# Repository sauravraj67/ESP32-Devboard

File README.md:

# ESP32-Devboard
I made a custom Esp32 board based on ESP32-S3-WROOM-1 , it has a USB type C and i tried to keep the size of the board as small as possible and to have as much as useful pins available on the board.
<br>

<br>
## Overview
This project is a **compact 2-layer development board** based on the **ESP32-S3-WROOM-1 module**. It exposes **all usable GPIOs**, includes onboard **3.3V regulation**, and USB connectivity for easy programming and prototyping. 

## Features
- ESP32-S3-WROOM-1 module (Wi-Fi + Bluetooth 5.0)
- 2-layer compact PCB
- USB connection for programming and power
- Onboard 3.3V voltage regulation

- ## Bill of Materials (BOM)
- 
| Qty | Description |  Total (USD) |
|----|-------------|-------------|
| 1 | PCB and Assembly  |   	71.97 |
| 1 |Shipping JLCPCB - Discount  | 1.72 |

### 💰 Cost Summary
 
- **Estimated Total Cost:** **$73.69 USD**

## Schematic & PCB

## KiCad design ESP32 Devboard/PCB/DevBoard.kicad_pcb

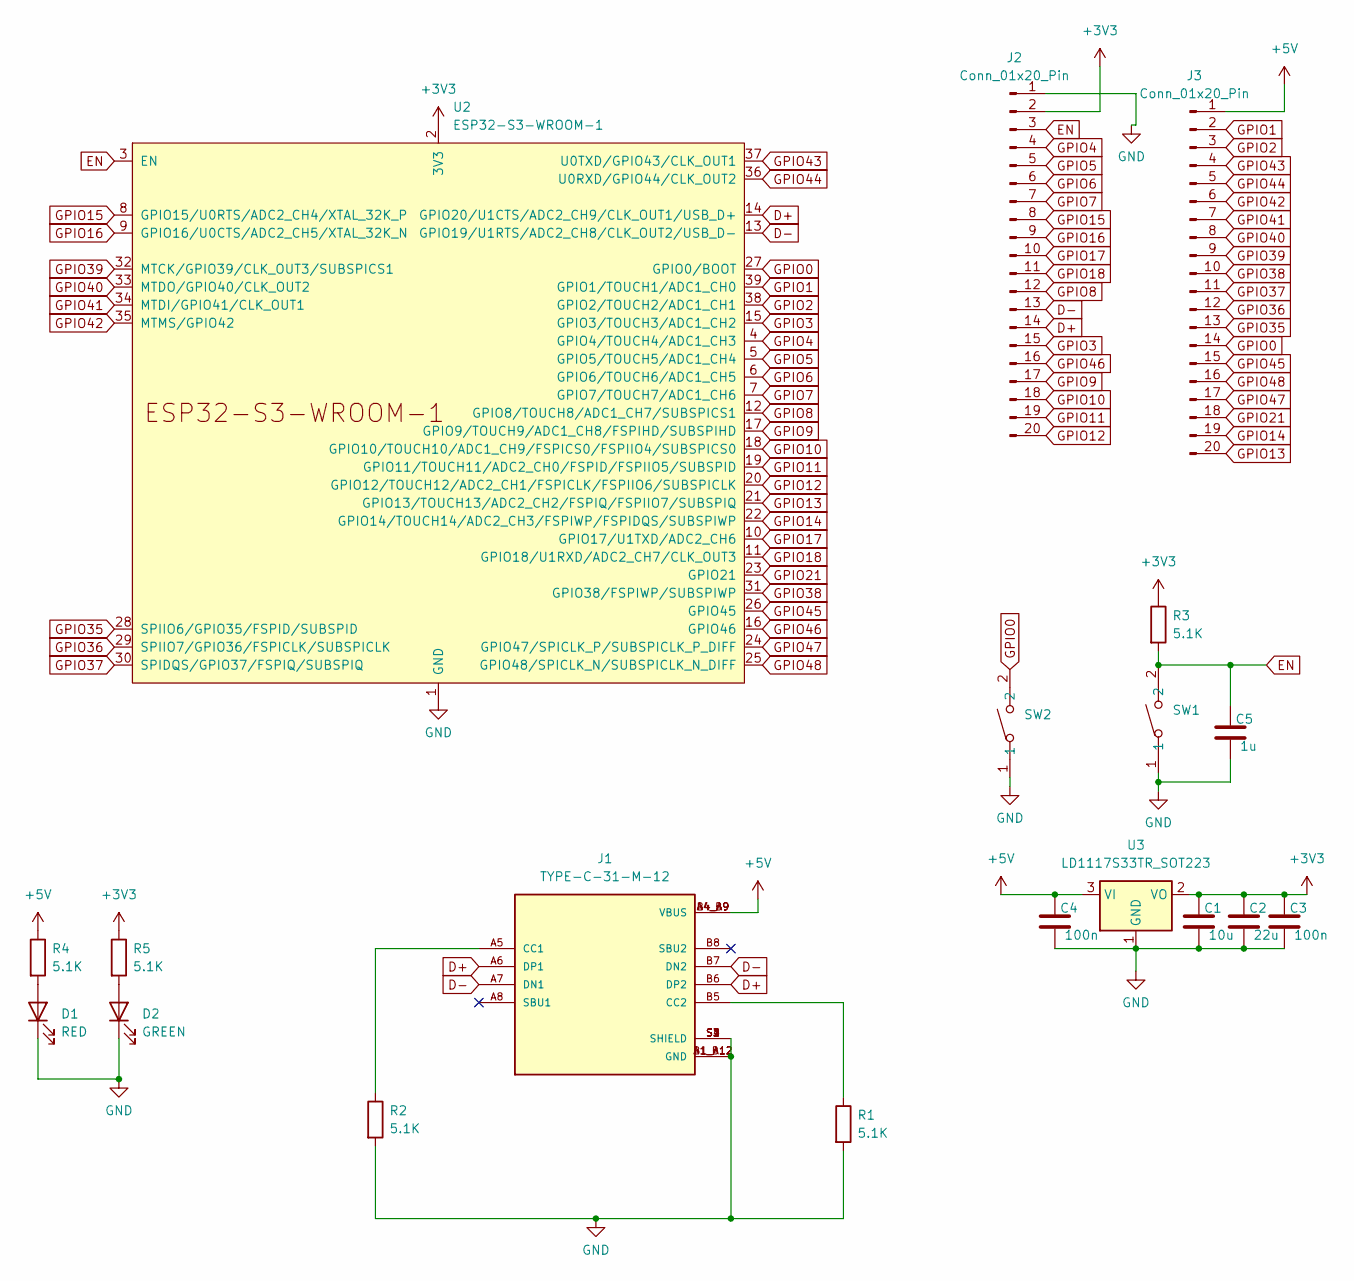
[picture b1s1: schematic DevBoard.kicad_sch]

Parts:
C1: 10u; C_0603_1608Metric
C2: 22u; C_0603_1608Metric
C3, C4: 100n; C_0603_1608Metric
C5: 1u; C_0603_1608Metric
D1: RED; LED_0603_1608Metric
D2: GREEN; LED_0603_1608Metric
J1: TYPE-C-31-M-12; HRO_TYPE-C-31-M-12; PARTREV 2020.12.08
J2, J3: Conn_01x20_Pin; PinHeader_1x20_P2.54mm_Vertical
R1, R2, R3, R4, R5: 5.1K; R_0603_1608Metric
SW1, SW2: TS-1088-AR02016; SW-SMD_L3.9-W3.0-P4.45; LCSC Part C720477
U2: ESP32-S3-WROOM-1
U3: LD1117S33TR_SOT223; SOT-223-3_TabPin2

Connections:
+3V3: C1.1, C2.1, C3.1, J2.2, R3.1, R5.1, U2.2 (3V3), U3.2 (VO)
+5V: C4.1, J1.A4_B9 (VBUS), J1.B4_A9 (VBUS), J3.1, R4.1, U3.3 (VI)
D+: J1.A6 (DP1), J1.B6 (DP2), J2.14, U2.14 (GPIO20/U1CTS/ADC2_CH9/CLK_OUT1/USB_D+)
D-: J1.A7 (DN1), J1.B7 (DN2), J2.13, U2.13 (GPIO19/U1RTS/ADC2_CH8/CLK_OUT2/USB_D-)
EN: C5.1, J2.3, R3.2, SW1.2, U2.3 (EN)
GND: C1.2, C2.2, C3.2, C4.2, C5.2, D1.1 (K), D2.1 (K), J1.A1_B12 (GND), J1.B1_A12 (GND), J1.S1 (SHIELD), J1.S2 (SHIELD), J1.S3 (SHIELD), J1.S4 (SHIELD), J2.1, R1.2, R2.2, SW1.1, SW2.1, U2.1 (GND), U2.40 (GND), U2.41 (GND), U3.1 (GND)
GPIO0: J3.14, SW2.2, U2.27 (GPIO0/BOOT)
GPIO1: J3.2, U2.39 (GPIO1/TOUCH1/ADC1_CH0)
GPIO2: J3.3, U2.38 (GPIO2/TOUCH2/ADC1_CH1)
GPIO3: J2.15, U2.15 (GPIO3/TOUCH3/ADC1_CH2)
GPIO4: J2.4, U2.4 (GPIO4/TOUCH4/ADC1_CH3)
GPIO5: J2.5, U2.5 (GPIO5/TOUCH5/ADC1_CH4)
GPIO6: J2.6, U2.6 (GPIO6/TOUCH6/ADC1_CH5)
GPIO7: J2.7, U2.7 (GPIO7/TOUCH7/ADC1_CH6)
GPIO8: J2.12, U2.12 (GPIO8/TOUCH8/ADC1_CH7/SUBSPICS1)
GPIO9: J2.17, U2.17 (GPIO9/TOUCH9/ADC1_CH8/FSPIHD/SUBSPIHD)
GPIO10: J2.18, U2.18 (GPIO10/TOUCH10/ADC1_CH9/FSPICS0/FSPIIO4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)
GPIO11: J2.19, U2.19 (GPIO11/TOUCH11/ADC2_CH0/FSPID/FSPIIO5/S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)
GPIO12: J2.20, U2.20 (GPIO12/TOUCH12/ADC2_CH1/FSPICLK/FSPIIO6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)
GPIO13: J3.20, U2.21 (GPIO13/TOUCH13/ADC2_CH2/FSPIQ/FSPIIO7/S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)
GPIO14: J3.19, U2.22 (GPIO14/TOUCH14/ADC2_CH3/FSPIWP/FSPIDQS/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)
GPIO15: J2.8, U2.8 (GPIO15/U0RTS/ADC2_CH4/XTAL_32K_P)
GPIO16: J2.9, U2.9 (GPIO16/U0CTS/ADC2_CH5/XTAL_32K_N)
GPIO17: J2.10, U2.10 (GPIO17/U1TXD/ADC2_CH6)
GPIO18: J2.11, U2.11 (GPIO18/U1RXD/ADC2_CH7/CLK_OUT3)
GPIO21: J3.18, U2.23 (GPIO21)
GPIO35: J3.13, U2.28 (SPIIO6/GPIO35/FSPID/SUBSPID)
GPIO36: J3.12, U2.29 (SPIIO7/GPIO36/FSPICLK/SUBSPICLK)
GPIO37: J3.11, U2.30 (SPIDQS/GPIO37/FSPIQ/SUBSPIQ)
GPIO38: J3.10, U2.31 (GPIO38/FSPIWP/SUBSPIWP)
GPIO39: J3.9, U2.32 (MTCK/GPIO39/CLK_OUT3/SUBSPICS1)
GPIO40: J3.8, U2.33 (MTDO/GPIO40/CLK_OUT2)
GPIO41: J3.7, U2.34 (MTDI/GPIO41/CLK_OUT1)
GPIO42: J3.6, U2.35 (MTMS/GPIO42)
GPIO43: J3.4, U2.37 (U0TXD/GPIO43/CLK_OUT1)
GPIO44: J3.5, U2.36 (U0RXD/GPIO44/CLK_OUT2)
GPIO45: J3.15, U2.26 (GPIO45)
GPIO46: J2.16, U2.16 (GPIO46)
GPIO47: J3.17, U2.24 (GPIO47/SPICLK_P/SUBSPICLK_P_DIFF)
GPIO48: J3.16, U2.25 (GPIO48/SPICLK_N/SUBSPICLK_N_DIFF)
unnamed: D1.2 (A), R4.2
unnamed: D2.2 (A), R5.2
unnamed: J1.A5 (CC1), R2.1
unnamed: J1.B5 (CC2), R1.1

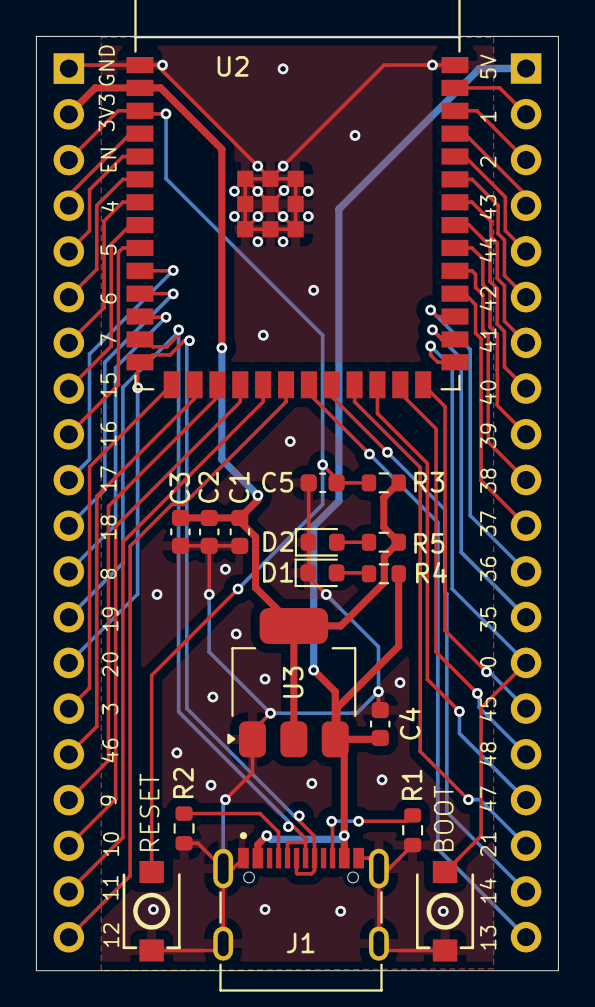
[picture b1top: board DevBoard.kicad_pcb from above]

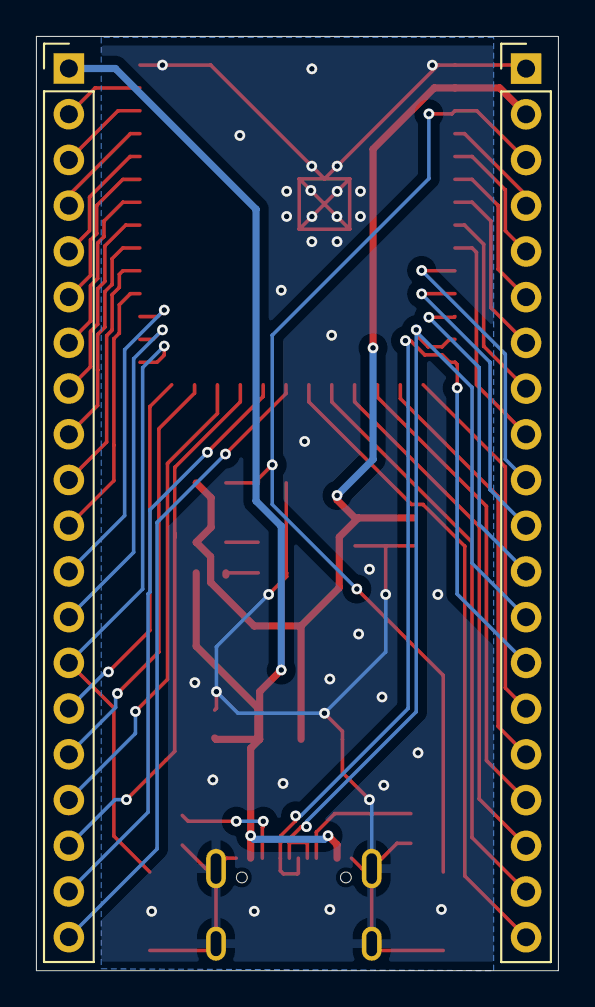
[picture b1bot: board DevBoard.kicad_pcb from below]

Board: 2 copper layers, 29.0 x 51.9 mm, 19 parts (2 on the bottom side), 44 nets.

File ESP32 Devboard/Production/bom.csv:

Designator,Footprint,Quantity,Value,LCSC Part #
C1,0603,1,10u,
C2,0603,1,22u,
"C3, C4",0603,2,100n,
C5,0603,1,1u,
D1,0603,1,RED,
D2,0603,1,GREEN,
J1,HRO_TYPE-C-31-M-12,1,TYPE-C-31-M-12,
"J2, J3",PinHeader_1x20_P2.54mm_Vertical,2,Conn_01x20_Pin,
"R1, R2, R3, R4, R5",0603,5,5.1K,
"SW1, SW2",SW-SMD_L3.9-W3.0-P4.45,2,TS-1088-AR02016,C720477
U2,ESP32-S3-WROOM-1,1,ESP32-S3-WROOM-1,
U3,SOT-223-3_TabPin2,1,LD1117S33TR_SOT223,
